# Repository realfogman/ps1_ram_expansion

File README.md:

# IBM PS/1 (model 2121) 4MB Memory Expansion
This is a 4MB memory expansion card for the IBM PS/1 model 2121 with a Intel 80386 CPU.
The schematic was done in Kicad (https://www.kicad.org/).

The memory expansion board was tested with CheckIt 3.0.
The memory ICs (2x IC41C16100S-50KG) can be found on different platforms and are still cheaply available.

# Disclaimer and attention
Although the board works for me in my setup, don't make me responsible if it does not work for you, or (in the worst case scenario) if it breaks your PC.
This is a hobbyist project with no guarantee of functionality!

Please don't forget to close the solder jumpers according to the top view.
Otherwise, the IBM PS/1 won't or wrongly detects the inserted RAM size.

In order to fit the board into the memory extension slot, don't forget to cut the connector board between D13 and D14 (according to the image).
Please, watch out to not cut any traces!

# Issues and improvements
My first attempt was quick and dirty (missing drilling file and mirrored text on the pcb bottom side) ;(

Luckily JLCPCB (https://jlcpcb.com/) checked my design and we could resolve these issues.

The Memory ICs have multiple VCC pins, which should be decoupled with 100nF capacitors each.
These capacitors could be located on the bottom side of the PCB board.
In the initial project release, only one 100nF capacitor is used.

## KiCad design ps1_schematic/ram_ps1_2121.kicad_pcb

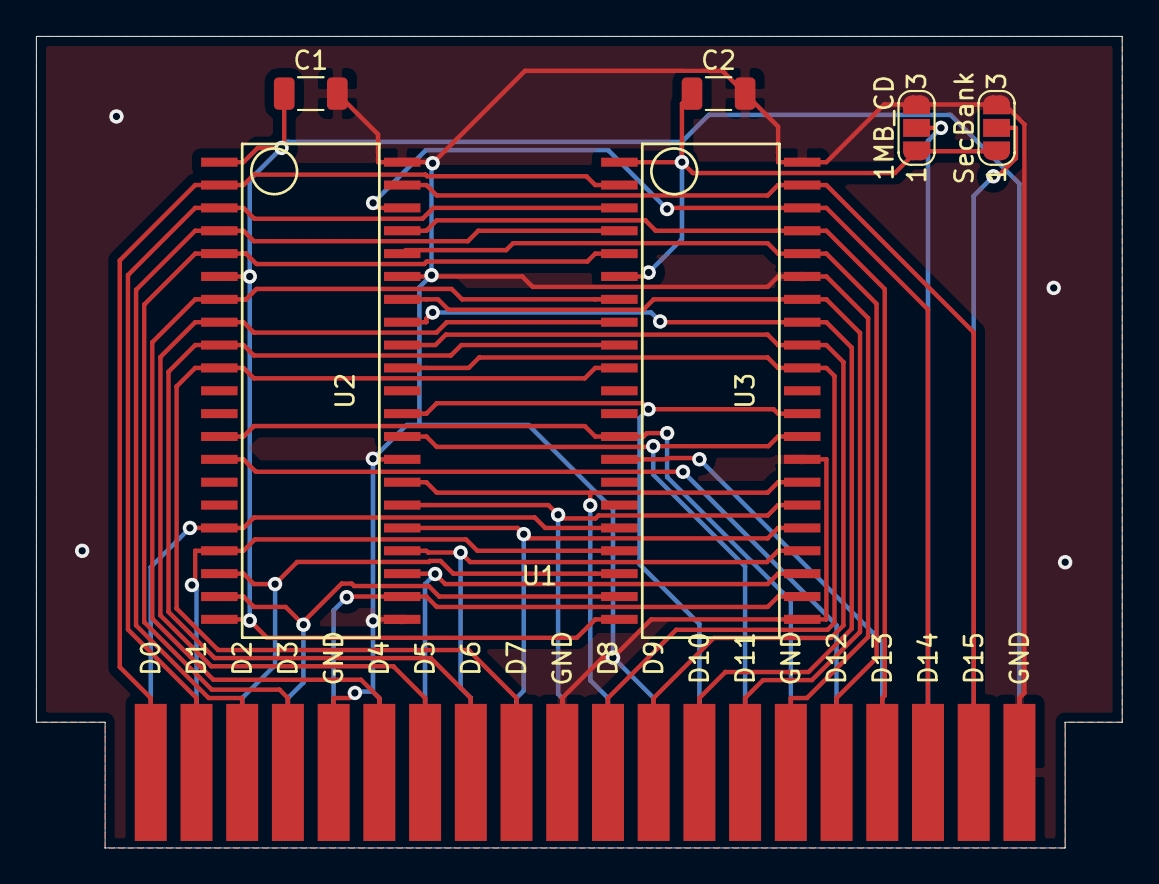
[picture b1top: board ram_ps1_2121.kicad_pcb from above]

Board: 2 copper layers, 60.3 x 45.1 mm, 7 parts (0 on the bottom side), 35 nets.

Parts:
1MB_CD: SolderJumper_3_Open; SolderJumper-3_P1.3mm_Open_RoundedPad1.0x1.5mm_NumberLabels
C1, C2: 100N; C_1206_3216Metric
SecBank: SolderJumper_3_Open; SolderJumper-3_P1.3mm_Open_RoundedPad1.0x1.5mm_NumberLabels
U1: PS1_RAM_Port; PS1_Expansion_Connector
U2, U3: IC41C16100S; SOJ-42

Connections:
/A0: U1.40, U2.17, U3.17
/A1: U1.39, U2.18, U3.18
/A2: U1.38, U2.19, U3.19
/A3: U1.37, U2.20, U3.20
/A4: U1.36, U2.23, U3.23
/A5: U1.34, U2.24, U3.24
/A6: U1.33, U2.25, U3.25
/A7: U1.32, U2.26, U3.26
/A8: U1.31, U2.27, U3.27
/A9: U1.30, U2.28, U3.28
/D0: U1.1, U2.2, U3.2
/D1: U1.2, U2.3, U3.3
/D2: U1.3, U2.4, U3.4
/D3: U1.4, U2.5, U3.5
/D4: U1.6, U2.7, U3.7
/D5: U1.7, U2.8, U3.8
/D6: U1.8, U2.9, U3.9
/D7: U1.9, U2.10, U3.10
/D8: U1.11, U2.33, U3.33
/D9: U1.12, U2.34, U3.34
/D10: U1.13, U2.35, U3.35
/D11: U1.14, U2.36, U3.36
/D12: U1.16, U2.38, U3.38
/D13: U1.17, U2.39, U3.39
/D14: U1.18, U2.40, U3.40
/D15: U1.19, U2.41, U3.41
/LCAS: U1.28, U2.31, U3.31
/RAS0: U1.25, U2.14
/RAS1: U1.24, U3.14
/UCAS: U1.27, U2.30, U3.30
/WE: U1.26, U2.13, U3.13
GND: 1MB_CD.3, C1.2, C2.2, SecBank.3, U1.5, U1.10, U1.15, U1.20, U1.29, U1.35, U2.22, U2.29, U2.37, U2.42, U3.22, U3.29, U3.37, U3.42
unnamed: SecBank.2, U1.22
unnamed: 1MB_CD.2, U1.23
VCC: 1MB_CD.1, C1.1, C2.1, SecBank.1, U1.21, U2.1, U2.6, U2.21, U3.1, U3.6, U3.21

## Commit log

2022-01-09 Update LICENSE
2022-01-09 Added schematic and gerber files.
2022-01-09 Added picture files.
2022-01-09 Added better description
2022-01-09 Added scaled picture files.
2022-01-09 Scaled picture files (again).
